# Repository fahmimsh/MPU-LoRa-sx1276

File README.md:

# MPU-LoRa-sx1276 ESP32 as GATEWAY and Arduino Promini as node multi connection communication
let's get developt it together
This repository program is used for monitoring public transportation such as metroline, MPU, and so on. There are 2 programs, namely node programs installed in vehicles by sending GPS data and gateway programs to receive data from node x vehicles to be sent to the database. Then the passenger android application will be able to find out the location of the vehicle closest to the location of the passenger vehicle.

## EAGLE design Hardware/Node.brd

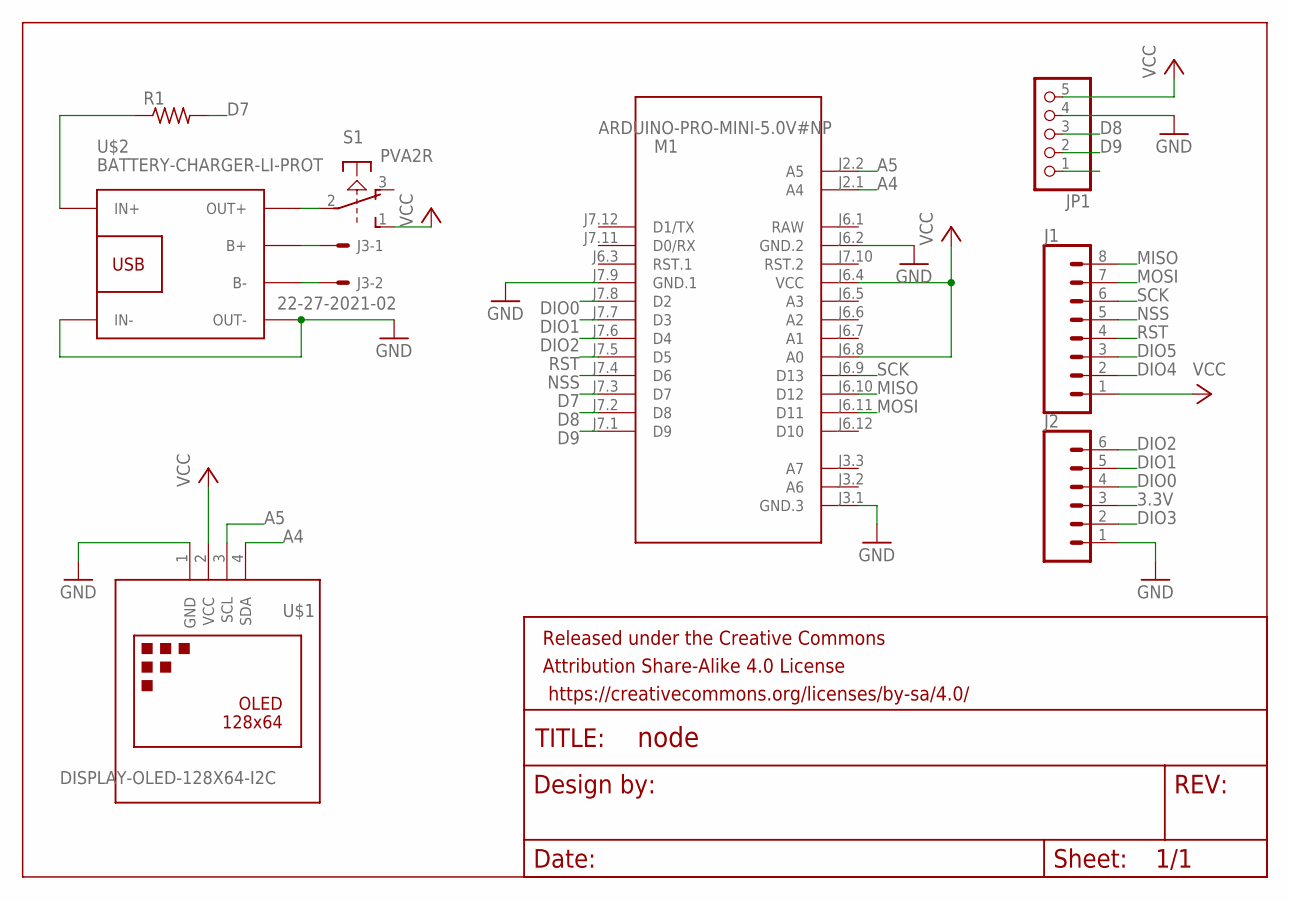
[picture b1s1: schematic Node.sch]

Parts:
FRAME1: FRAME-LEDGER; CREATIVE_COMMONS
J1: CONN_08"; 1X08
J2: CONN_06SILK_FEMALE_PTH; 1X06
J3: 22-27-2021-02; 6410-02
JP1: PINHD-1X5/90; 1X05/90
M1: ARDUINO-PRO-MINI-5.0V#NP; ARDUINO-PRO-MINI#NP
R1: R-US_R1206; R1206
S1: PVA2R
U$1: DISPLAY-OLED-128X64-I2C
U$2: BATTERY-CHARGER-LI-PROT

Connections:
3.3V: J2.3
A4: M1.J2.1 (A4), U$1.4 (SDA)
A5: M1.J2.2 (A5), U$1.3 (SCL)
D7: M1.J7.3 (D7), R1.2
D8: JP1.3, M1.J7.2 (D8)
D9: JP1.2, M1.J7.1 (D9)
DIO0: J2.4, M1.J7.8 (D2)
DIO1: J2.5, M1.J7.7 (D3)
DIO2: J2.6, M1.J7.6 (D4)
DIO3: J2.2
DIO4: J1.2
DIO5: J1.3
GND: J2.1, JP1.4, M1.J3.1 (GND.3), M1.J6.2 (GND.2), M1.J7.9 (GND.1), U$1.1 (GND), U$2.IN-, U$2.OUT-
MISO: J1.8, M1.J6.10 (D12)
MOSI: J1.7, M1.J6.11 (D11)
unnamed: R1.1, U$2.IN+
unnamed: J3.1, U$2.B+
unnamed: J3.2, U$2.B-
unnamed: S1.2, U$2.OUT+
NSS: J1.5, M1.J7.4 (D6)
RAW: M1.J6.1 (RAW)
RST: J1.4, M1.J7.5 (D5)
SCK: J1.6, M1.J6.9 (D13)
VCC: J1.1, JP1.5, M1.J6.4 (VCC), M1.J6.8 (A0), S1.1 (S), U$1.2 (VCC)

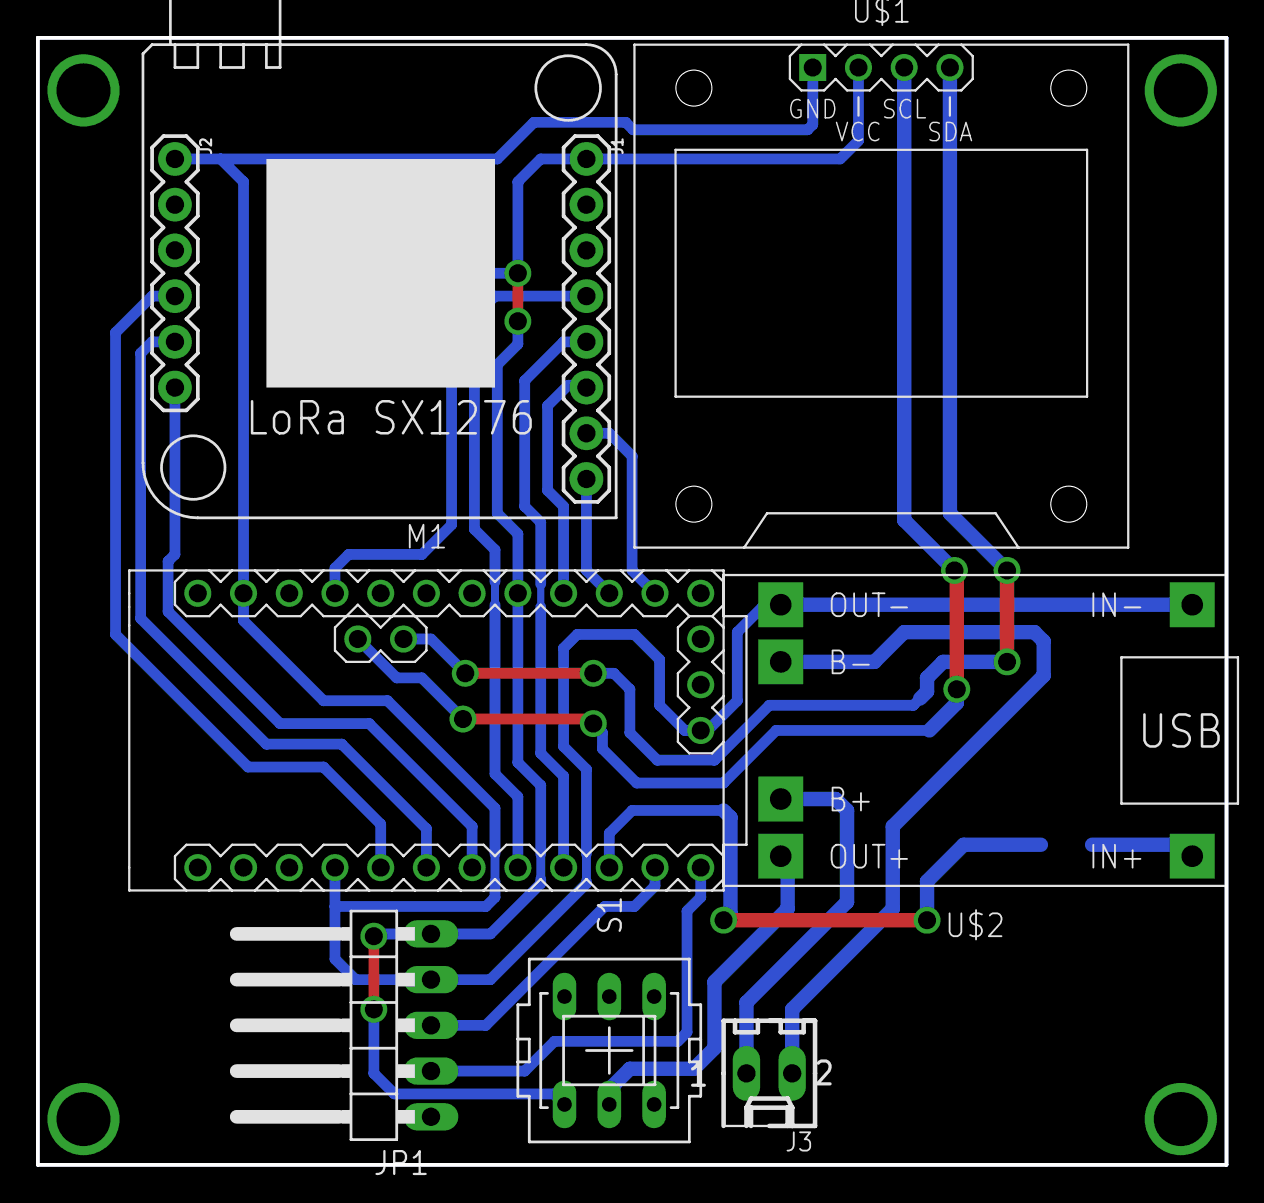
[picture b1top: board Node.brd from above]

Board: 2 copper layers, 66.0 x 62.6 mm, 10 parts (1 on the bottom side), 19 nets.

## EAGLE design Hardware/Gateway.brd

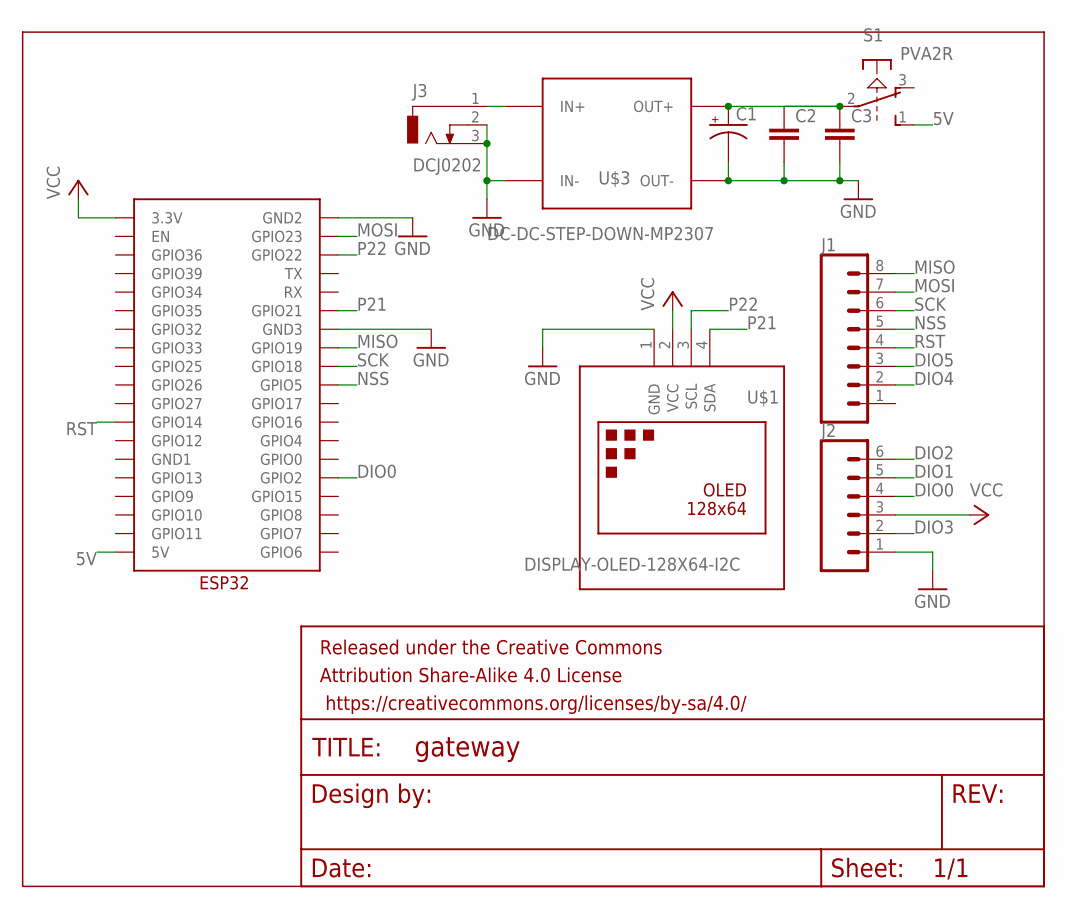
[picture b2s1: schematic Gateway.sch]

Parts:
C1: CPOL-USE2,5-6E; E2,5-6E
C2, C3: C-EUC1206; C1206
FRAME1: FRAME-LEDGER; CREATIVE_COMMONS
J1: CONN_08"; 1X08
J2: CONN_06SILK_FEMALE_PTH; 1X06
J3: DCJ0202
S1: PVA2R
U$1: DISPLAY-OLED-128X64-I2C
U$2: ESP32
U$3: DC-DC-STEP-DOWN-MP2307

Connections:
5V: S1.1 (S), U$2.5V
DIO0: J2.4, U$2.GPIO2
DIO1: J2.5
DIO2: J2.6
DIO3: J2.2
DIO4: J1.2
DIO5: J1.3
GND: C1.-, C2.2, C3.2, J2.1, J3.2, J3.3, U$1.1 (GND), U$2.GND2, U$2.GND3, U$3.IN-, U$3.OUT-
MISO: J1.8, U$2.GPIO19
MOSI: J1.7, U$2.GPIO23
unnamed: C1.+, C2.1, C3.1, S1.2, U$3.OUT+
unnamed: J3.1, U$3.IN+
NSS: J1.5, U$2.GPIO5
P21: U$1.4 (SDA), U$2.GPIO21
P22: U$1.3 (SCL), U$2.GPIO22
RST: J1.4, U$2.GPIO14
SCK: J1.6, U$2.GPIO18
VCC: J2.3, U$1.2 (VCC), U$2.3.3V

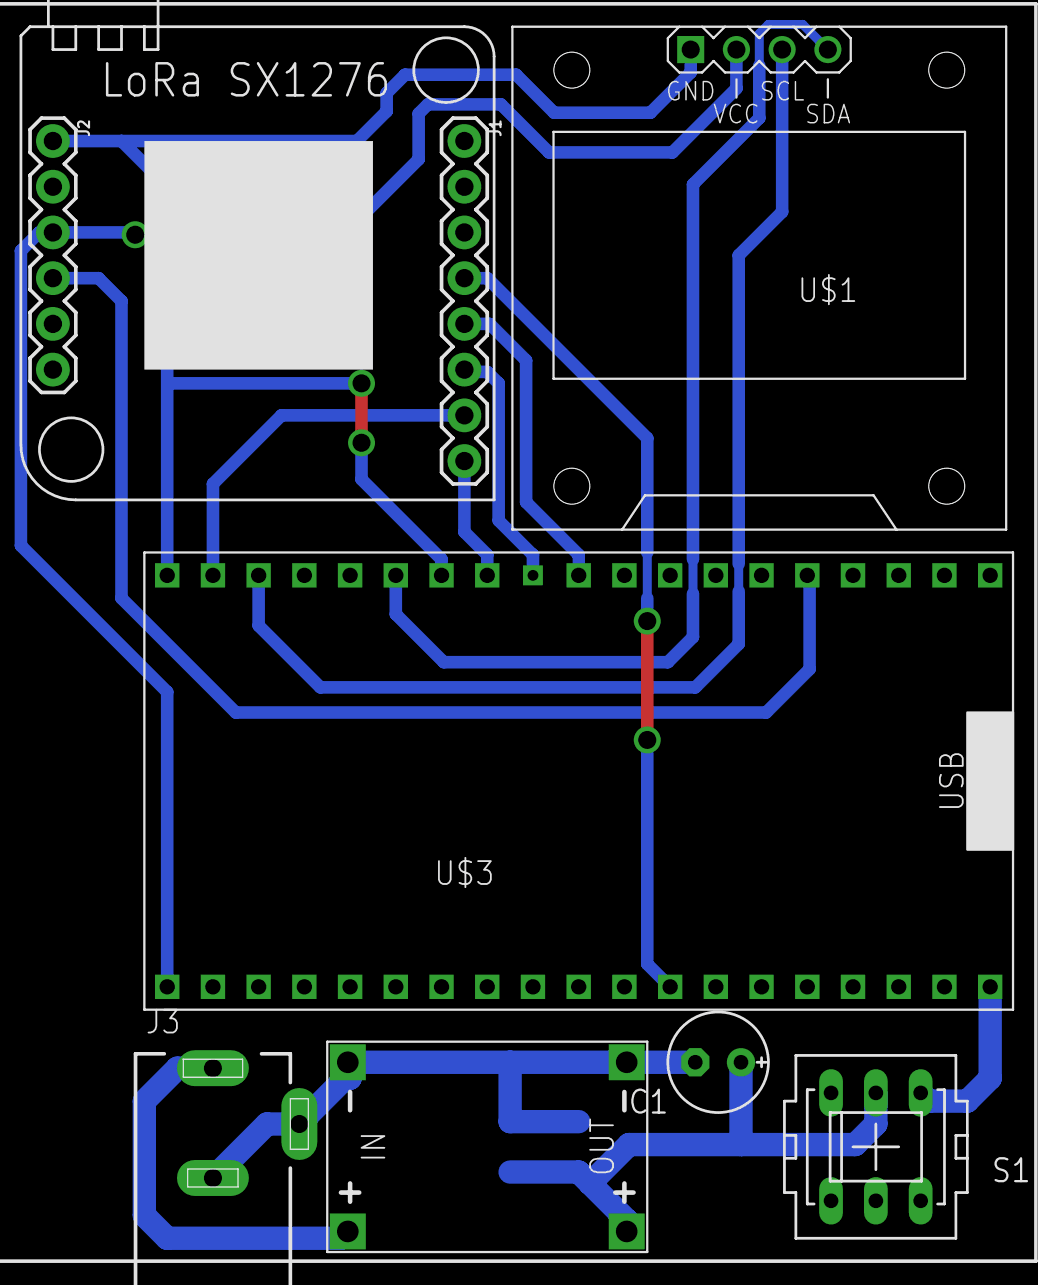
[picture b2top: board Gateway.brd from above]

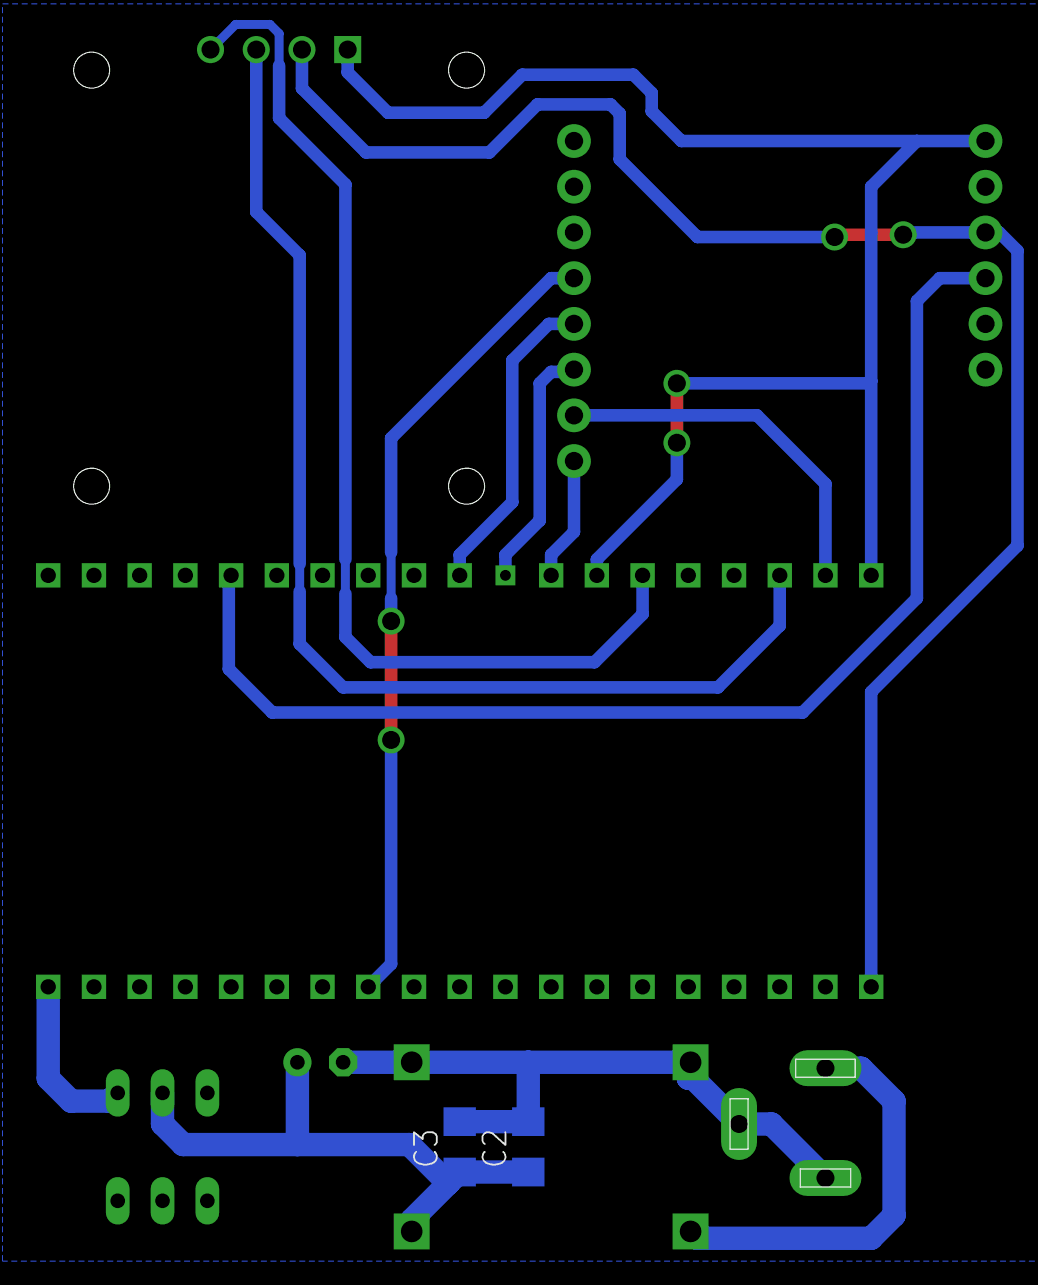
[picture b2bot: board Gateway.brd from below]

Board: 2 copper layers, 11 parts (2 on the bottom side), 13 nets.

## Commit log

2021-04-20 belumselesai
2021-05-26 updatev1

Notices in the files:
parts and their libraries:
SparkFun-Connectors: Licensing: Creative Commons ShareAlike 4.0 International - https://creativecommons.org/licenses/by-sa/4.0
diy-modules: Released under the Creative Commons Attribution 4.0 International License: http://creativecommons.org/licenses/by/4.0
